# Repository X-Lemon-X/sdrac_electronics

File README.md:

# SDRAC electronic design
This repository contains the psb schematics and designs of the SDRAC board.

## SDRACboard
- Supply voltage 12-48V (9-55V)
- the board has a 5V/2A on board regualator, to power the board and peripherals
- USB-C for programming and reading data
- ST-wire pins for programming and debugging
- 3 bit hardware address CID0, CID1, CID2
- 6 pin JS connector for IO-appliacitons, with analog, UART, Timers, 5V and GND
- 2x 4 pin Molex connectors for CAN bus
- 2x 6 pin Molex connectors for I2C magnetic encoder
- 2x 2 pin Molex connectors for external temperature sensors (ntc termistors)
- 1x 4 pin Molex connector for stepper motor
- 1x 4 pin connector for external steper motor driver
- 1x Screw terminal for external steper motor driver power
- XT30-M, XT30-F  connectors for input and output power

## Schematics
The schematics are made in KiCad.

## Assembly
Manual assembly takes about 2 hours, with stemple and hot air station.

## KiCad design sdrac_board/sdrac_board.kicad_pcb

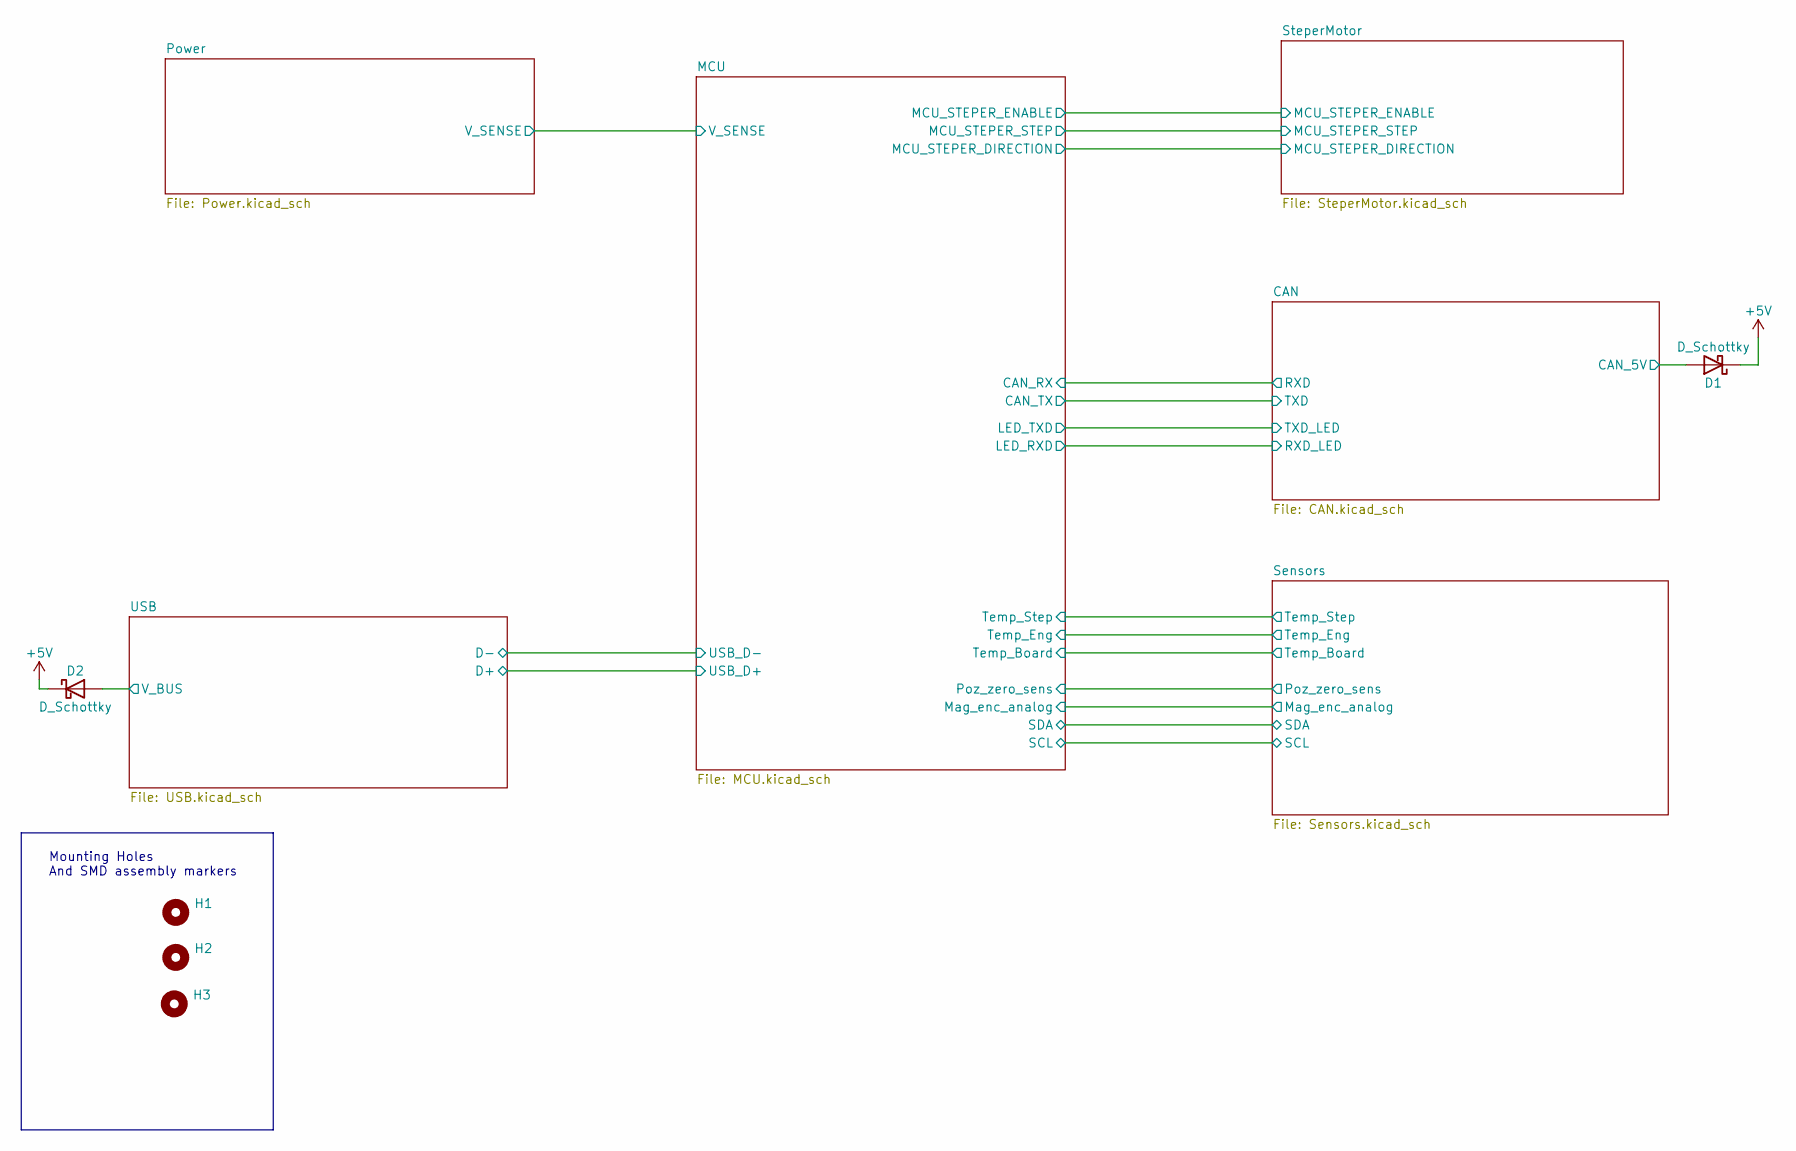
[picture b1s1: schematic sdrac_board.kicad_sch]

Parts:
D1, D2: D_Schottky; D_SMA
H1, H2, H3: MountingHole; MountingHole_3.2mm_M3_ISO7380

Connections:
+5V: D1.1 (K), D2.1 (K); also elsewhere on the board
/CAN/CAN_5V: D1.2 (A); also elsewhere on the board
/USB/V_BUS: D2.2 (A); also elsewhere on the board

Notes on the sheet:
Mounting Holes And SMD assembly markers

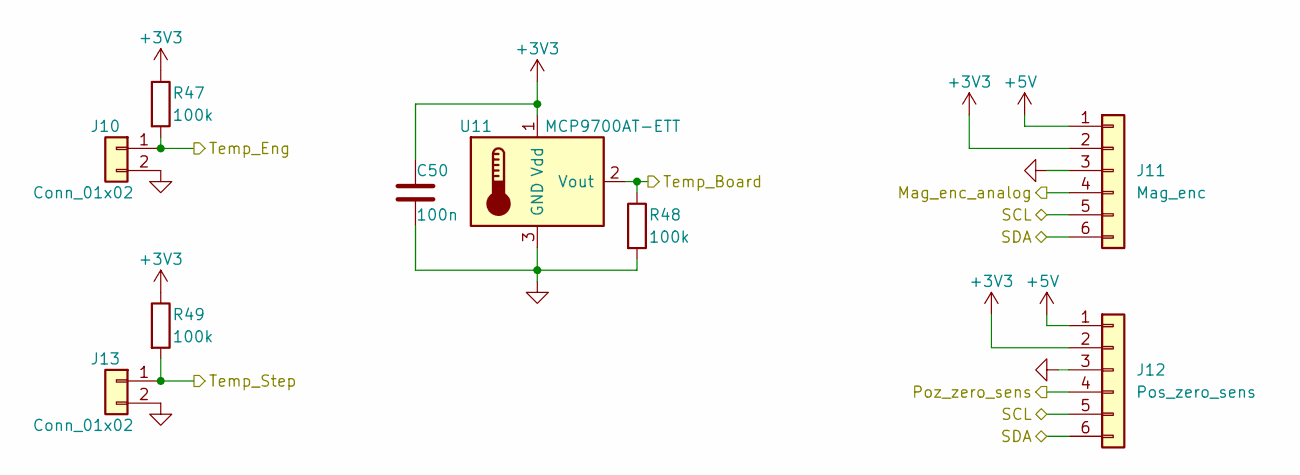
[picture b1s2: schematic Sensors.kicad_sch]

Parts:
C50: 100n; C_0402_1005Metric
J10, J13: Conn_01x02; Molex_Micro-Fit_3.0_43045-0212_2x01_P3.00mm_Vertical
J11: Mag_enc; Molex_Micro-Fit_3.0_43045-0612_2x03_P3.00mm_Vertical
J12: Pos_zero_sens; Molex_Micro-Fit_3.0_43045-0612_2x03_P3.00mm_Vertical
R47, R48, R49: 100k; R_0402_1005Metric
U11: MCP9700AT-ETT; SOT-23

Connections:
+3V3: C50.1, J11.2, J12.2, R47.1, R49.1, U11.1 (Vdd); also elsewhere on the board
+5V: J11.1, J12.1; also elsewhere on the board
/MCU/Mag_enc_analog: J11.4; also elsewhere on the board
/MCU/Poz_zero_sens: J12.4; also elsewhere on the board
/MCU/SCL: J11.5, J12.5; also elsewhere on the board
/MCU/SDA: J11.6, J12.6; also elsewhere on the board
/MCU/Temp_Board: R48.1, U11.2 (Vout); also elsewhere on the board
/MCU/Temp_Eng: J10.1, R47.2; also elsewhere on the board
/MCU/Temp_Step: J13.1, R49.2; also elsewhere on the board
GND: C50.2, J10.2, J11.3, J12.3, J13.2, R48.2, U11.3 (GND); also elsewhere on the board

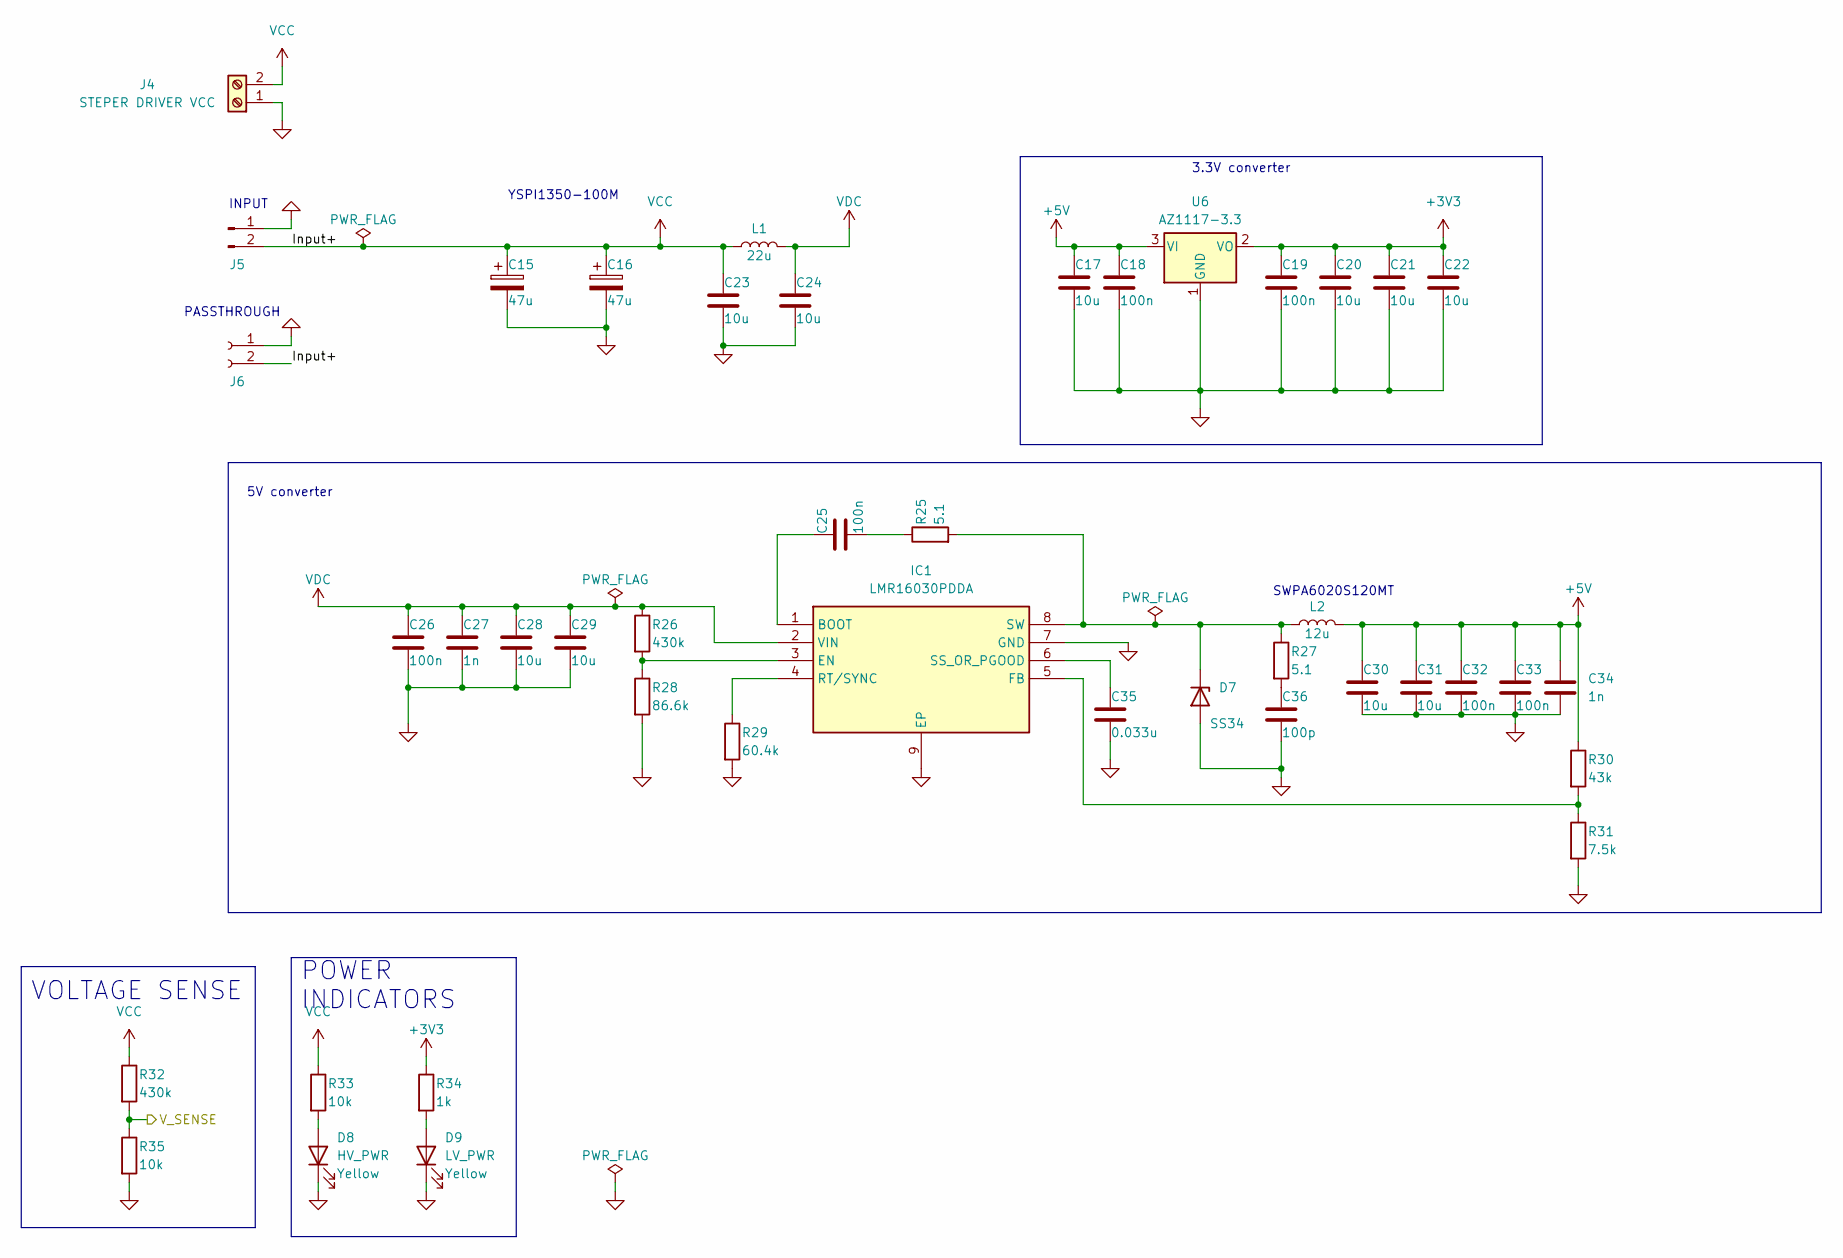
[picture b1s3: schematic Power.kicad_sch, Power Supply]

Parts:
C15, C16: 47u; CP_Elec_10x10.5
C17: 10u; C_1206_3216Metric
C18, C19, C26, C32, C33: 100n; C_0603_1608Metric
C20, C21, C22, C30, C31: 10u; C_0805_2012Metric
C23, C24, C28, C29: 10u; C_1210_3225Metric
C25: 100n; R_0603_1608Metric
C27, C34: 1n; C_0603_1608Metric
C35: 0.033u; R_0603_1608Metric
C36: 100p; C_0603_1608Metric
D7: SS34; D_SMA
D8: HV_PWR; D_0603_1608Metric
D9: LV_PWR; D_0603_1608Metric
IC1: LMR16030PDDA; SOIC127P600X170-9N; Manufacturer_Part_Number LMR16030PDDA; Mouser Part Number 595-LMR16030PDDA
J4: STEPER DRIVER VCC; TerminalBlock_Phoenix_MKDS-1,5-2_1x02_P5.00mm_Horizontal
J5: Conn_01x02_Male; AMASS_XT30PW-M_1x02_P2.50mm_Horizontal
J6: Conn_01x02_Female; AMASS_XT30PW-F_1x02_P2.50mm_Horizontal
L1: 22u; L_6.3x6.3_H3
L2: 12u; L_1812_4532Metric
R25, R27: 5.1; R_0603_1608Metric
R26, R32: 430k; R_0603_1608Metric
R28: 86.6k; R_0603_1608Metric
R29: 60.4k; R_0603_1608Metric
R30: 43k; R_0603_1608Metric
R31: 7.5k; R_0603_1608Metric
R33: 10k; R_0402_1005Metric
R34: 1k; R_0402_1005Metric
R35: 10k; R_0603_1608Metric
U6: AZ1117-3.3; SOT-223-3_TabPin2

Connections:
+3V3: C19.1, C20.1, C21.1, C22.1, R34.1, U6.2 (VO); also elsewhere on the board
+5V: C17.1, C18.1, C30.1, C31.1, C32.1, C33.1, C34.1, L2.2, R30.1, U6.3 (VI); also elsewhere on the board
/MCU/V_SENSE: R32.2, R35.1; also elsewhere on the board
GND: C15.2, C16.2, C17.2, C18.2, C19.2, C20.2, C21.2, C22.2, C23.2, C24.2, C26.2, C27.2, C28.2, C29.2, C30.2, C31.2, C32.2, C33.2, C34.2, C35.2, C36.2, D7.2 (A), D8.1 (K), D9.1 (K), IC1.7 (GND), IC1.9 (EP), J4.1, J5.1, J6.1, R28.2, R29.2, R31.2, R35.2, U6.1 (GND); also elsewhere on the board
unnamed: C25.2, R25.1
unnamed: C36.1, R27.2
unnamed: D7.1 (K), IC1.8 (SW), L2.1, R25.2, R27.1
unnamed: D8.2 (A), R33.2
unnamed: D9.2 (A), R34.2
unnamed: C25.1, IC1.1 (BOOT)
unnamed: IC1.3 (EN), R26.2, R28.1
unnamed: IC1.5 (FB), R30.2, R31.1
unnamed: IC1.4 (RT/SYNC), R29.1
unnamed: C35.1, IC1.6 (SS_OR_PGOOD)
VCC: C15.1, C16.1, C23.1, J4.2, J5.2, J6.2, L1.1, R32.1, R33.1; also elsewhere on the board
VDC: C24.1, C26.1, C27.1, C28.1, C29.1, IC1.2 (VIN), L1.2, R26.1

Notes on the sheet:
POWER INDICATORS
VOLTAGE SENSE
YSPI1350-100M
PASSTHROUGH
SWPA6020S120MT
INPUT
3.3V converter
5V converter

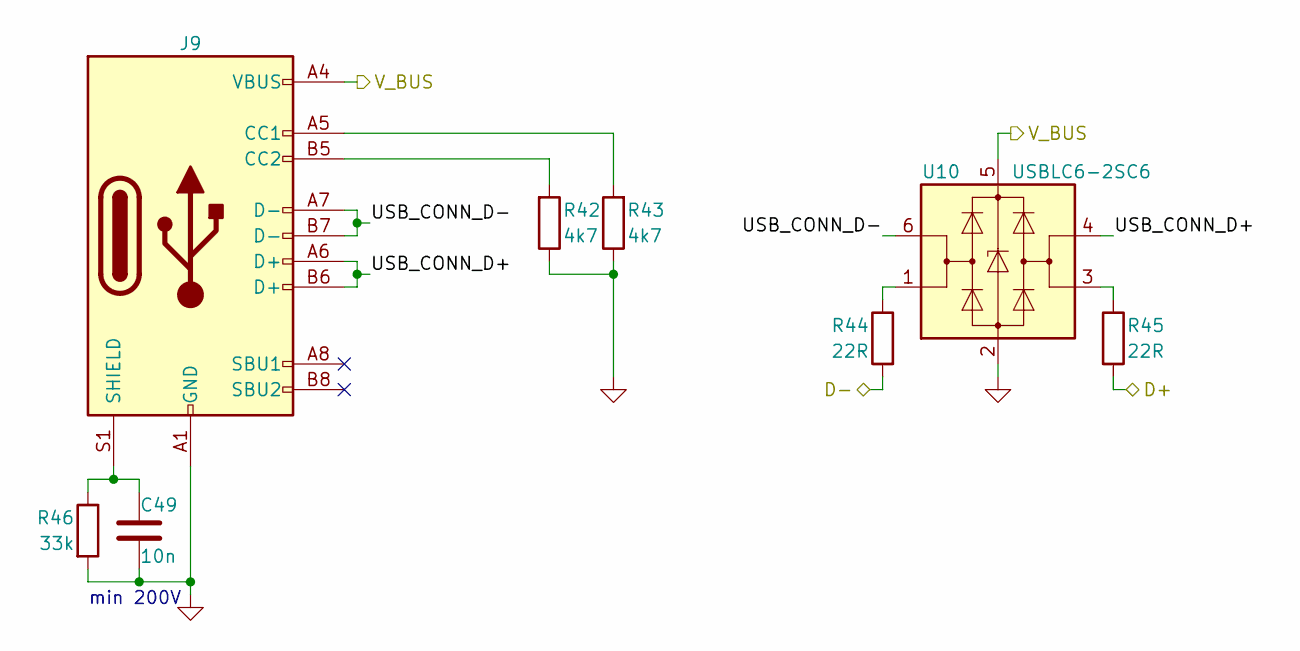
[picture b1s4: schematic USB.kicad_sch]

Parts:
C49: 10n; C_0805_2012Metric
J9: USB_C_Receptacle_USB2.0; USB_C_Receptacle_G-Switch_GT-USB-7010ASV
R42, R43: 4k7; R_0402_1005Metric
R44, R45: 22R; R_0402_1005Metric
R46: 33k; R_0603_1608Metric
U10: USBLC6-2SC6; SOT-23-6

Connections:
/MCU/USB_D+: R45.2; also elsewhere on the board
/MCU/USB_D-: R44.2; also elsewhere on the board
/USB/USB_CONN_D+: J9.A6 (D+), J9.B6 (D+), U10.4 (I/O2)
/USB/USB_CONN_D-: J9.A7 (D-), J9.B7 (D-), U10.6 (I/O1)
/USB/V_BUS: J9.A4 (VBUS), J9.A9 (VBUS), J9.B4 (VBUS), J9.B9 (VBUS), U10.5 (VBUS); also elsewhere on the board
GND: C49.2, J9.A1 (GND), J9.A12 (GND), J9.B1 (GND), J9.B12 (GND), R42.1, R43.1, R46.2, U10.2 (GND); also elsewhere on the board
unnamed: J9.A5 (CC1), R43.2
unnamed: J9.B5 (CC2), R42.2
unnamed: C49.1, J9.S1 (SHIELD), R46.1
unnamed: R44.1, U10.1 (I/O1)
unnamed: R45.1, U10.3 (I/O2)

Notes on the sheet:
min 200V

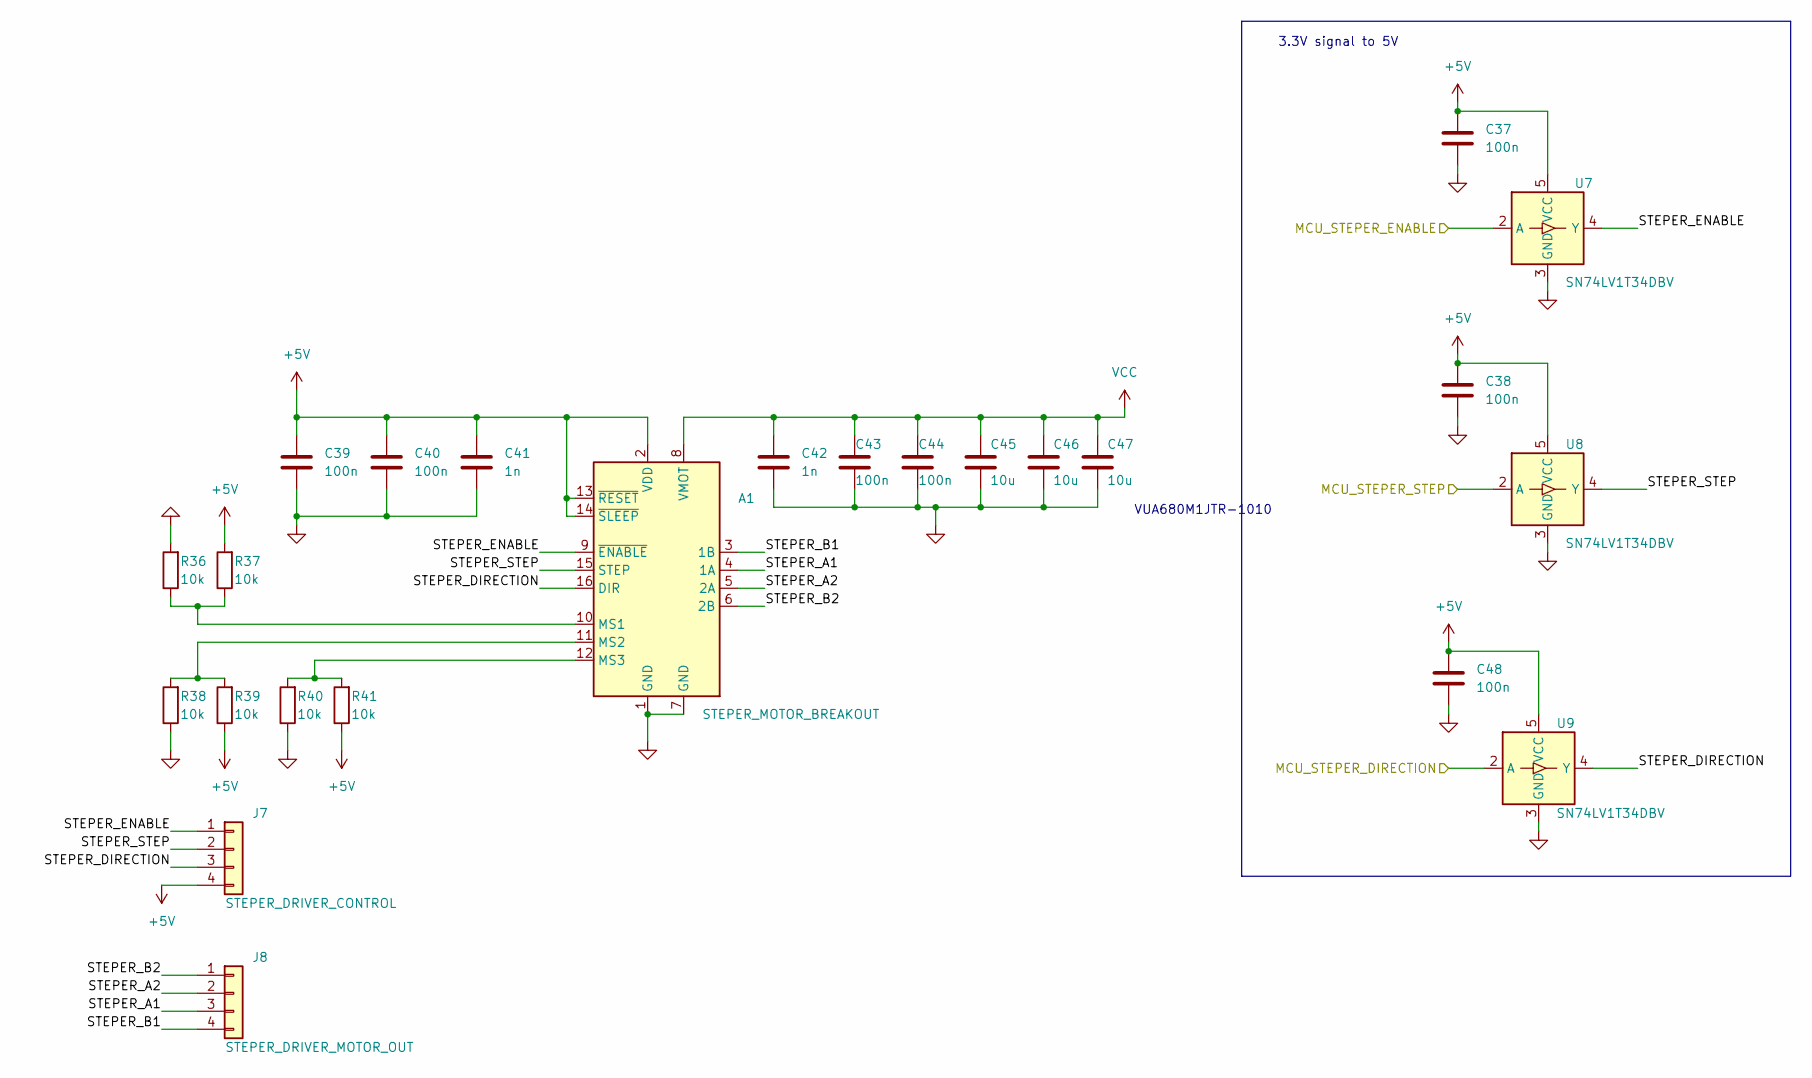
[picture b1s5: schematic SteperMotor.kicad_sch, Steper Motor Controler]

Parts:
A1: STEPER_MOTOR_BREAKOUT; Pololu_Breakout-16_15.2x20.3mm
C37, C38, C48: 100n; C_0402_1005Metric
C39, C40: 100n; C_0402_1005Metric_Pad0.74x0.62mm_HandSolder
C41: 1n; C_0402_1005Metric
C42: 1n; C_1206_3216Metric
C43, C44: 100n; C_1206_3216Metric
C45, C46, C47: 10u; C_1210_3225Metric
J7: STEPER_DRIVER_CONTROL; Molex_Micro-Fit_3.0_43045-0412_2x02_P3.00mm_Vertical
J8: STEPER_DRIVER_MOTOR_OUT; Molex_Micro-Fit_3.0_43045-0412_2x02_P3.00mm_Vertical
R36, R37, R38, R39, R40, R41: 10k; R_0402_1005Metric
U7, U8, U9: SN74LV1T34DBV; SOT-23-5

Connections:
+5V: A1.2 (VDD), A1.13 (~RESET), A1.14 (~SLEEP), C37.1, C38.1, C39.1, C40.1, C41.1, C48.1, J7.4, R37.2, R39.1, R41.1, U7.5 (VCC), U8.5 (VCC), U9.5 (VCC); also elsewhere on the board
/MCU/MCU_STEPER_DIRECTION: U9.2 (A); also elsewhere on the board
/MCU/MCU_STEPER_ENABLE: U7.2 (A); also elsewhere on the board
/MCU/MCU_STEPER_STEP: U8.2 (A); also elsewhere on the board
/SteperMotor/STEPER_A1: A1.4 (1A), J8.3
/SteperMotor/STEPER_A2: A1.5 (2A), J8.2
/SteperMotor/STEPER_B1: A1.3 (1B), J8.4
/SteperMotor/STEPER_B2: A1.6 (2B), J8.1
/SteperMotor/STEPER_DIRECTION: A1.16 (DIR), J7.3, U9.4 (Y)
/SteperMotor/STEPER_ENABLE: A1.9 (~ENABLE), J7.1, U7.4 (Y)
/SteperMotor/STEPER_STEP: A1.15 (STEP), J7.2, U8.4 (Y)
GND: A1.1 (GND), A1.7 (GND), C37.2, C38.2, C39.2, C40.2, C41.2, C42.2, C43.2, C44.2, C45.2, C46.2, C47.2, C48.2, R36.2, R38.1, R40.1, U7.3 (GND), U8.3 (GND), U9.3 (GND); also elsewhere on the board
unnamed: A1.10 (MS1), R36.1, R37.1
unnamed: A1.11 (MS2), R38.2, R39.2
unnamed: A1.12 (MS3), R40.2, R41.2
VCC: A1.8 (VMOT), C42.1, C43.1, C44.1, C45.1, C46.1, C47.1; also elsewhere on the board

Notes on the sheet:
3.3V signal to 5V
VUA680M1JTR-1010

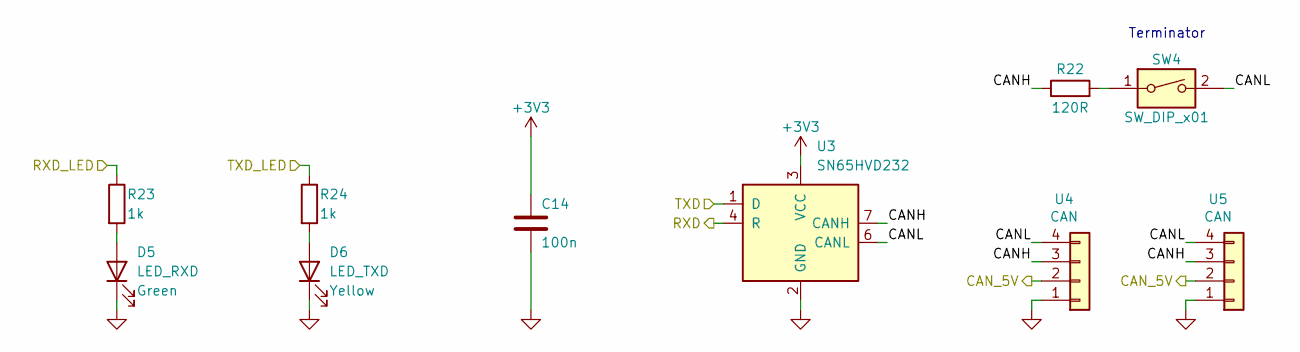
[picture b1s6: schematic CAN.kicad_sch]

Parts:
C14: 100n; C_0402_1005Metric
D5: LED_RXD; D_0603_1608Metric
D6: LED_TXD; D_0603_1608Metric
R22: 120R; R_0603_1608Metric
R23, R24: 1k; R_0402_1005Metric
SW4: SW_DIP_x01; SW_DIP_SPSTx01_Slide_6.7x4.1mm_W6.73mm_P2.54mm_LowProfile_J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
U3: SN65HVD232; SOIC-8_3.9x4.9mm_P1.27mm
U4, U5: CAN; Molex_Micro-Fit_3.0_43045-0412_2x02_P3.00mm_Vertical

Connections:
+3V3: C14.1, U3.3 (VCC); also elsewhere on the board
/CAN/CANH: R22.1, U3.7 (CANH), U4.3, U5.3
/CAN/CANL: SW4.2, U3.6 (CANL), U4.4, U5.4
/CAN/CAN_5V: U4.2, U5.2; also elsewhere on the board
/CAN/RXD: U3.4 (R); also elsewhere on the board
/CAN/RXD_LED: R23.1; also elsewhere on the board
/CAN/TXD: U3.1 (D); also elsewhere on the board
/CAN/TXD_LED: R24.1; also elsewhere on the board
GND: C14.2, D5.1 (K), D6.1 (K), U3.2 (GND), U4.1, U5.1; also elsewhere on the board
unnamed: D5.2 (A), R23.2
unnamed: D6.2 (A), R24.2
unnamed: R22.2, SW4.1

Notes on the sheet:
Terminator

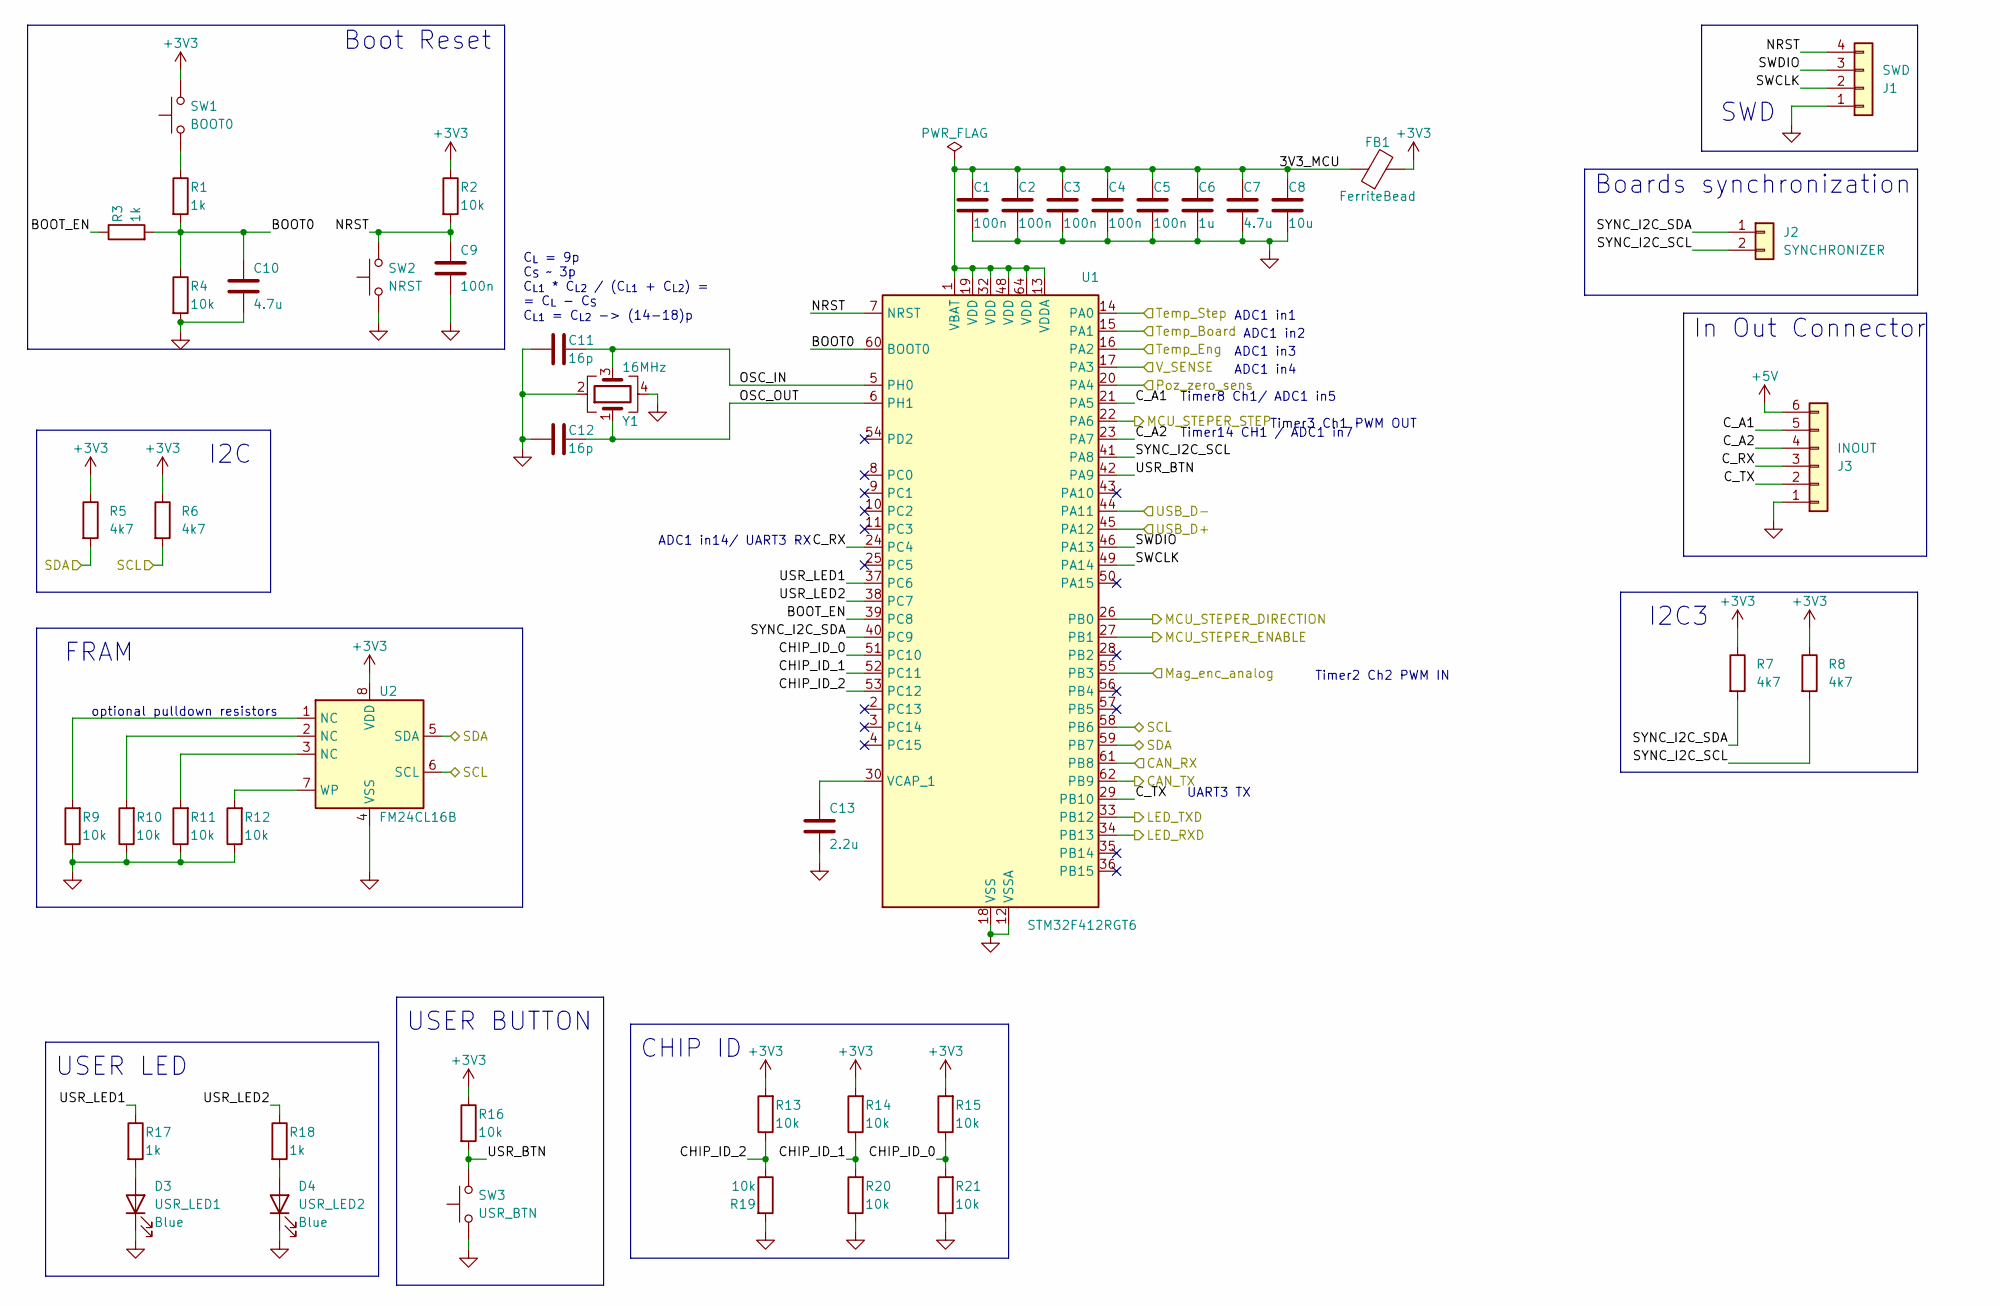
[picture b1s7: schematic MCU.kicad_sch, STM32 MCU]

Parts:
C1, C2, C3, C4, C5, C9: 100n; C_0402_1005Metric
C6: 1u; C_0603_1608Metric
C7: 4.7u; C_0603_1608Metric
C8: 10u; C_0805_2012Metric
C10: 4.7u; C_0402_1005Metric
C11, C12: 16p; C_0402_1005Metric
C13: 2.2u; C_0603_1608Metric
D3: USR_LED1; D_0603_1608Metric
D4: USR_LED2; D_0603_1608Metric
FB1: FerriteBead; L_0805_2012Metric
J1: SWD; PinHeader_1x04_P2.54mm_Vertical
J2: SYNCHRONIZER; JST_XH_B2B-XH-A_1x02_P2.50mm_Vertical
J3: INOUT; JST_XH_B6B-XH-A_1x06_P2.50mm_Vertical
R1, R3, R17, R18: 1k; R_0402_1005Metric
R2, R4, R9, R10, R11, R12, R13, R14, R15, R16, R19, R20, R21: 10k; R_0402_1005Metric
R5, R6, R7, R8: 4k7; R_0402_1005Metric
SW1: BOOT0; SW_SPST_PTS810
SW2: NRST; SW_SPST_PTS810
SW3: USR_BTN; SW_SPST_PTS810
U1: STM32F412RGT6; LQFP-64_10x10mm_P0.5mm
U2: FM24CL16B; SOIC-8_3.9x4.9mm_P1.27mm
Y1: 16MHz; Crystal_SMD_3225-4Pin_3.2x2.5mm

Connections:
+3V3: FB1.2, R2.1, R5.1, R6.1, R7.1, R8.1, R13.2, R14.2, R15.2, R16.1, SW1.2, U2.8 (VDD); also elsewhere on the board
+5V: J3.6; also elsewhere on the board
/CAN/RXD: U1.61 (PB8); also elsewhere on the board
/CAN/RXD_LED: U1.34 (PB13); also elsewhere on the board
/CAN/TXD: U1.62 (PB9); also elsewhere on the board
/CAN/TXD_LED: U1.33 (PB12); also elsewhere on the board
/MCU/3V3_MCU: C1.1, C2.1, C3.1, C4.1, C5.1, C6.1, C7.1, C8.1, FB1.1, U1.1 (VBAT), U1.13 (VDDA), U1.19 (VDD), U1.32 (VDD), U1.48 (VDD), U1.64 (VDD)
/MCU/BOOT0: C10.1, R1.2, R3.2, R4.1, U1.60 (BOOT0)
/MCU/BOOT_EN: R3.1, U1.39 (PC8)
/MCU/CHIP_ID_0: R15.1, R21.2, U1.51 (PC10)
/MCU/CHIP_ID_1: R14.1, R20.2, U1.52 (PC11)
/MCU/CHIP_ID_2: R13.1, R19.1, U1.53 (PC12)
/MCU/C_A1: J3.5, U1.21 (PA5)
/MCU/C_A2: J3.4, U1.23 (PA7)
/MCU/C_RX: J3.3, U1.24 (PC4)
/MCU/C_TX: J3.2, U1.29 (PB10)
/MCU/MCU_STEPER_DIRECTION: U1.26 (PB0); also elsewhere on the board
/MCU/MCU_STEPER_ENABLE: U1.27 (PB1); also elsewhere on the board
/MCU/MCU_STEPER_STEP: U1.22 (PA6); also elsewhere on the board
/MCU/Mag_enc_analog: U1.55 (PB3); also elsewhere on the board
/MCU/NRST: C9.1, J1.4, R2.2, SW2.2, U1.7 (NRST)
/MCU/OSC_IN: C11.2, U1.5 (PH0), Y1.3
/MCU/OSC_OUT: C12.2, U1.6 (PH1), Y1.1
/MCU/Poz_zero_sens: U1.20 (PA4); also elsewhere on the board
/MCU/SCL: R6.2, U1.58 (PB6), U2.6 (SCL); also elsewhere on the board
/MCU/SDA: R5.2, U1.59 (PB7), U2.5 (SDA); also elsewhere on the board
/MCU/SWCLK: J1.2, U1.49 (PA14)
/MCU/SWDIO: J1.3, U1.46 (PA13)
/MCU/SYNC_I2C_SCL: J2.2, R8.2, U1.41 (PA8)
/MCU/SYNC_I2C_SDA: J2.1, R7.2, U1.40 (PC9)
/MCU/Temp_Board: U1.15 (PA1); also elsewhere on the board
/MCU/Temp_Eng: U1.16 (PA2); also elsewhere on the board
/MCU/Temp_Step: U1.14 (PA0); also elsewhere on the board
/MCU/USB_D+: U1.45 (PA12); also elsewhere on the board
/MCU/USB_D-: U1.44 (PA11); also elsewhere on the board
/MCU/USR_BTN: R16.2, SW3.2, U1.42 (PA9)
/MCU/USR_LED1: R17.1, U1.37 (PC6)
/MCU/USR_LED2: R18.1, U1.38 (PC7)
/MCU/V_SENSE: U1.17 (PA3); also elsewhere on the board
GND: C1.2, C2.2, C3.2, C4.2, C5.2, C6.2, C7.2, C8.2, C9.2, C10.2, C11.1, C12.1, C13.2, D3.1 (K), D4.1 (K), J1.1, J3.1, R4.2, R9.1, R10.1, R11.1, R12.1, R19.2, R20.1, R21.1, SW2.1, SW3.1, U1.12 (VSSA), U1.18 (VSS), U1.31 (VSS), U1.47 (VSS), U1.63 (VSS), U2.4 (VSS), Y1.2, Y1.4; also elsewhere on the board
unnamed: D3.2 (A), R17.2
unnamed: D4.2 (A), R18.2
unnamed: R1.1, SW1.1
unnamed: R9.2, U2.1 (NC)
unnamed: R10.2, U2.2 (NC)
unnamed: R11.2, U2.3 (NC)
unnamed: C13.1, U1.30 (VCAP_1)
unnamed: R12.2, U2.7 (WP)

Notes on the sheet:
UART3 TX
FRAM
Timer2 Ch2 PWM IN
Timer3 Ch1 PWM OUT
C_{L} = 9p C_{S} ~ 3p C_{L1} * C_{L2} / (C_{L1} + C_{L2}) = = C_{L} - C_{S} C_{L1} = C_{L2} -> (14-18)p
In Out Connector
optional pulldown resistors
I2C3
Boot Reset
ADC1 in3
CHIP ID
Timer14 CH1 / ADC1 in7
SWD
USER LED
USER BUTTON
ADC1 in4
ADC1 in14/ UART3 RX
Timer8 Ch1/ ADC1 in5
ADC1 in1
ADC1 in2
I2C
Boards synchronization

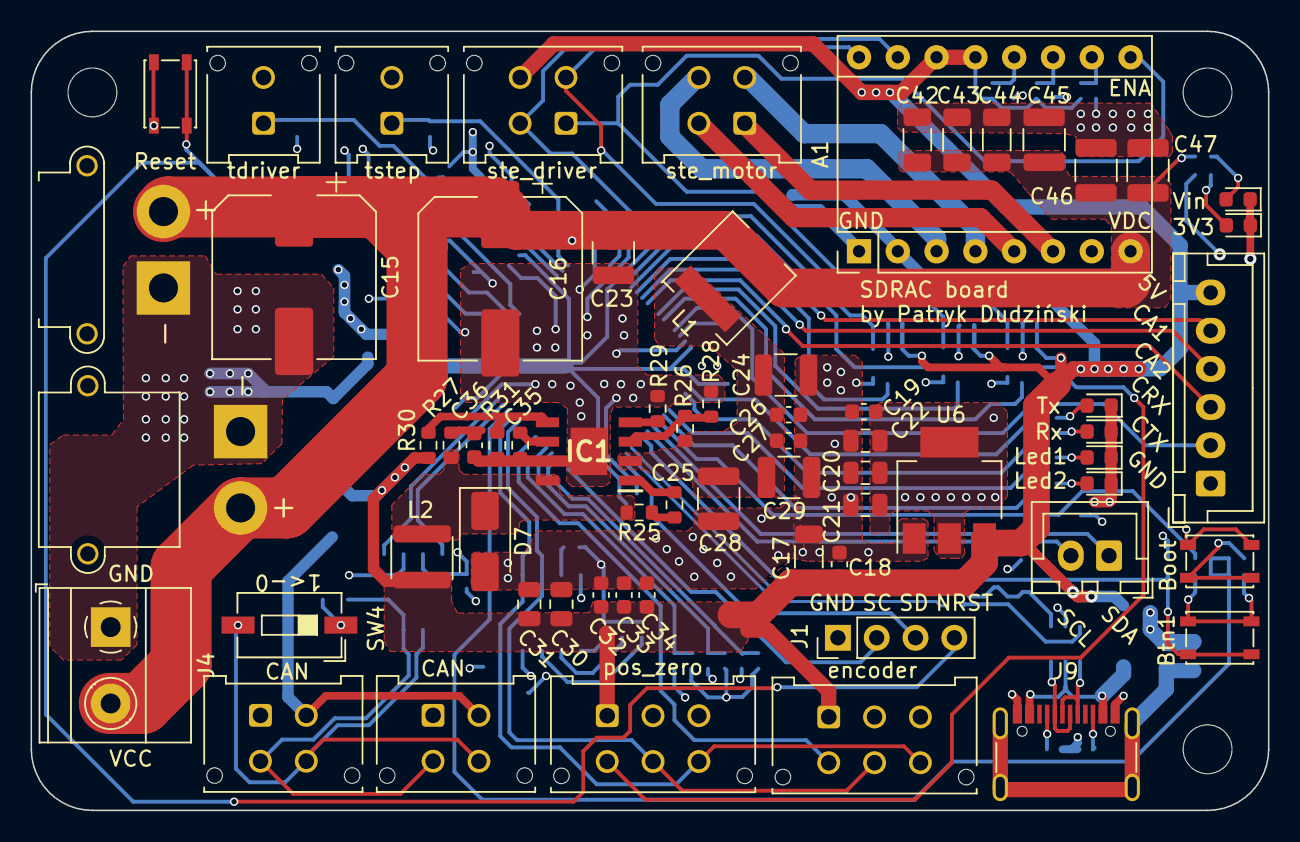
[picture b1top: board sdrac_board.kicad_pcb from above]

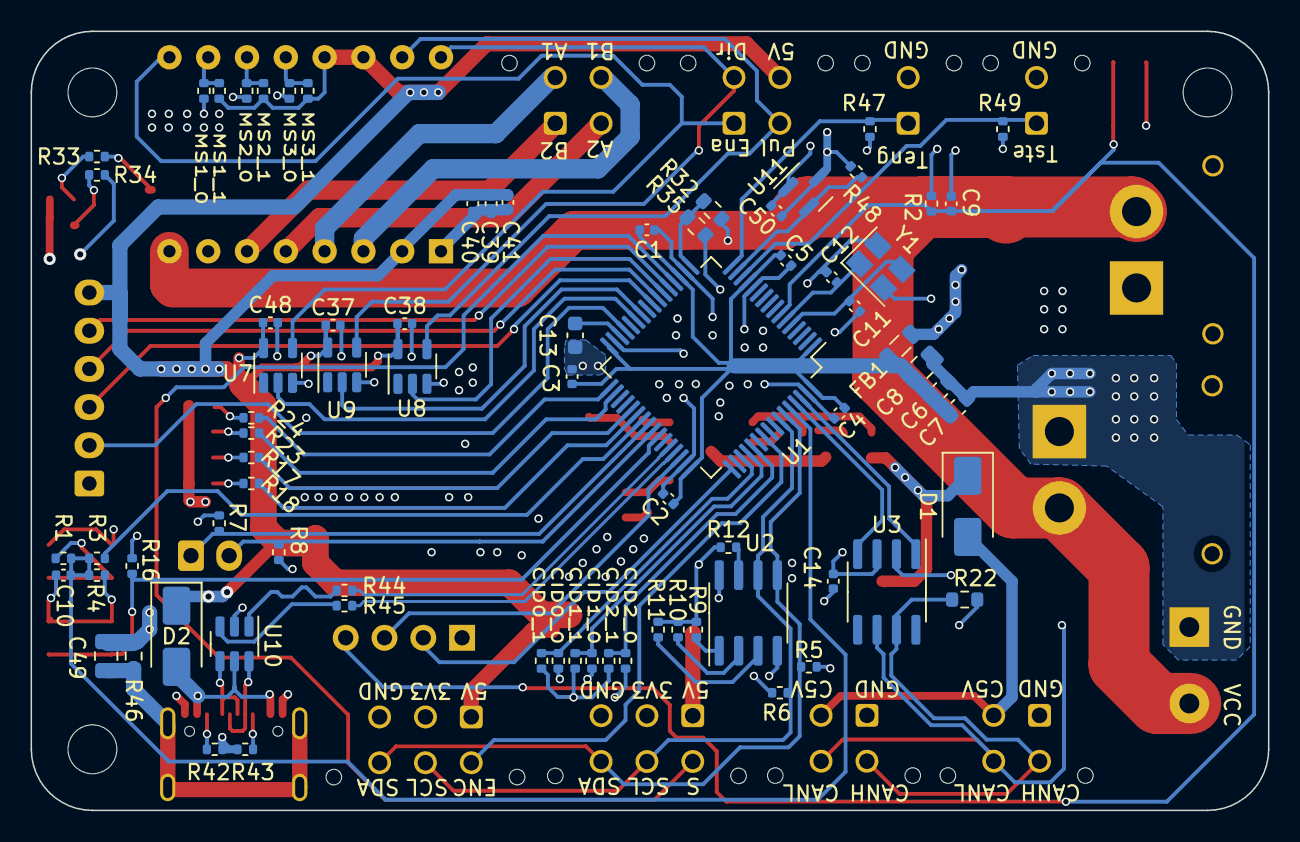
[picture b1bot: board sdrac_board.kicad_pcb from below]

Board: 4 copper layers, 81.0 x 51.0 mm, 145 parts (76 on the bottom side), 84 nets.

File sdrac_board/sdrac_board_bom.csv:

"Id";"Designator";"Footprint";"Quantity";"Designation";"Supplier and ref";
1;"R28";"R_0603_1608Metric";1;"86.6k";;;
2;"U4,U5";"Molex_Micro-Fit_3.0_43045-0412_2x02_P3.00mm_Vertical";2;"CAN";;;
3;"R29";"R_0603_1608Metric";1;"60.4k";;;
4;"U6";"SOT-223-3_TabPin2";1;"AZ1117-3.3";;;
5;"J6";"AMASS_XT30PW-F_1x02_P2.50mm_Horizontal";1;"Conn_01x02_Female";;;
6;"J8";"Molex_Micro-Fit_3.0_43045-0412_2x02_P3.00mm_Vertical";1;"STEPER_DRIVER_MOTOR_OUT";;;
7;"SW4";"SW_DIP_SPSTx01_Slide_6.7x4.1mm_W6.73mm_P2.54mm_LowProfile_JPin";1;"SW_DIP_x01";;;
8;"D6";"D_0603_1608Metric";1;"LED_TXD";;;
9;"C16,C15";"CP_Elec_10x10.5";2;"47u";;;
10;"J5";"AMASS_XT30PW-M_1x02_P2.50mm_Horizontal";1;"Conn_01x02_Male";;;
11;"R30,R32";"R_0603_1608Metric";2;"43k";;;
12;"C35";"R_0603_1608Metric";1;"0.033u";;;
13;"C33,C18,C26,C32,C19";"C_0603_1608Metric";5;"100n";;;
14;"C43,C44";"C_1206_3216Metric";2;"100n";;;
15;"C47,C23,C29,C28,C46,C24,C45";"C_1210_3225Metric";7;"10u";;;
16;"J12";"Molex_Micro-Fit_3.0_43045-0612_2x03_P3.00mm_Vertical";1;"Pos_zero_sens";;;
17;"D3";"D_0603_1608Metric";1;"USR_LED1";;;
18;"C25";"R_0603_1608Metric";1;"100n";;;
19;"C17";"C_1206_3216Metric";1;"10u";;;
20;"C34,C27";"C_0603_1608Metric";2;"1n";;;
21;"SW2";"SW_SPST_PTS810";1;"NRST";;;
22;"SW1";"SW_SPST_PTS810";1;"BOOT0";;;
23;"C30,C21,C31,C22,C20,C8";"C_0805_2012Metric";6;"10u";;;
24;"R26";"R_0603_1608Metric";1;"430k";;;
25;"R31";"R_0603_1608Metric";1;"7.5k";;;
26;"D7";"D_SMA";1;"SS34";;;
27;"SW3";"SW_SPST_PTS810";1;"USR_BTN";;;
28;"H1,H2,H3";"MountingHole_3.2mm_M3_ISO7380";3;"MountingHole";;;
29;"R27,R25";"R_0603_1608Metric";2;"5.1";;;
30;"J11";"Molex_Micro-Fit_3.0_43045-0612_2x03_P3.00mm_Vertical";1;"Mag_enc";;;
31;"IC1";"SOIC127P600X170-9N";1;"LMR16030PDDA";;;
32;"J1";"PinHeader_1x04_P2.54mm_Vertical";1;"SWD";;;
33;"J9";"USB_C_Receptacle_G-Switch_GT-USB-7010ASV";1;"USB_C_Receptacle_USB2.0";;;
34;"J7";"Molex_Micro-Fit_3.0_43045-0412_2x02_P3.00mm_Vertical";1;"STEPER_DRIVER_CONTROL";;;
35;"L1";"L_6.3x6.3_H3";1;"22u";;;
36;"J3";"JST_XH_B6B-XH-A_1x06_P2.50mm_Vertical";1;"INOUT";;;
37;"D9";"D_0603_1608Metric";1;"LV_PWR";;;
38;"D8";"D_0603_1608Metric";1;"HV_PWR";;;
39;"D4";"D_0603_1608Metric";1;"USR_LED2";;;
40;"L2";"L_1812_4532Metric";1;"12u";;;
41;"J4";"TerminalBlock_Phoenix_MKDS-1,5-2_1x02_P5.00mm_Horizontal";1;"STEPER DRIVER VCC";;;
42;"A1";"Pololu_Breakout-16_15.2x20.3mm";1;"STEPER_MOTOR_BREAKOUT";;;
43;"J10,J13";"Molex_Micro-Fit_3.0_43045-0212_2x01_P3.00mm_Vertical";2;"Conn_01x02";;;
44;"C36";"C_0603_1608Metric";1;"100p";;;
45;"D5";"D_0603_1608Metric";1;"LED_RXD";;;
46;"C42";"C_1206_3216Metric";1;"1n";;;
47;"J2";"JST_XH_B2B-XH-A_1x02_P2.50mm_Vertical";1;"SYNCHRONIZER";;;
48;"U3";"SOIC-8_3.9x4.9mm_P1.27mm";1;"SN65HVD232";;;
49;"R48,R47,R49";"R_0402_1005Metric";3;"100k";;;
50;"R6,R8,R7,R5";"R_0402_1005Metric";4;"4k7";;;
51;"C39,C40";"C_0402_1005Metric_Pad0.74x0.62mm_HandSolder";2;"100n";;;
52;"U7,U9,U8";"SOT-23-5";3;"SN74LV1T34DBV";;;
53;"U11";"SOT-23";1;"MCP9700AT-ETT";;;
54;"R3,R23,R34,R1,R17,R24,R18";"R_0402_1005Metric";7;"1k";;;
55;"R2,R4,R16,R19,R36,R13,R41,R20,R10,R15,R40,R39,R11,R12,R14,R33,R37,R9,R21,R38";"R_0402_1005Metric";20;"10k";;;
56;"R45,R44";"R_0402_1005Metric";2;"22R";;;
57;"R22";"R_0603_1608Metric";1;"120R";;;
58;"U1";"LQFP-64_10x10mm_P0.5mm";1;"STM32F412RGT6";;;
59;"R43,R42";"R_0402_1005Metric";2;"5k1";;;
60;"C2,C37,C9,C1,C50,C4,C14,C48,C5,C3,C38";"C_0402_1005Metric";11;"100n";;;
61;"D2,D1";"D_SMA";2;"D_Schottky";;;
62;"R46";"R_0603_1608Metric";1;"33k";;;
63;"C11,C12";"C_0402_1005Metric";2;"16p";;;
64;"C6";"C_0603_1608Metric";1;"1u";;;
65;"C49";"C_0805_2012Metric";1;"10n";;;
66;"R35";"R_0603_1608Metric";1;"1k";;;
67;"C41";"C_0402_1005Metric";1;"1n";;;
68;"C7";"C_0603_1608Metric";1;"4.7u";;;
69;"U10";"SOT-23-6";1;"USBLC6-2SC6";;;
70;"C10";"C_0402_1005Metric";1;"4.7u";;;
71;"C13";"C_0603_1608Metric";1;"2.2u";;;
72;"Y1";"Crystal_SMD_3225-4Pin_3.2x2.5mm";1;"16MHz";;;
73;"U2";"SOIC-8_3.9x4.9mm_P1.27mm";1;"FM24CL16B";;;
74;"FB1";"L_0805_2012Metric";1;"FerriteBead";;;

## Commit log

2024-03-08 init commit added all fiels
2024-03-12 fixed caps and added nreset
2024-03-15 added stuff
2024-03-15 added git ignore
2024-03-18 addded 6pin conenctor
2024-03-18 updated stuf
2024-03-20 stuff
2024-03-20 made critical changes
2024-04-15 nothing done
2024-04-17 added second I2C communscation lane for synchronization and added wyas to change mcirosteping with resistors
2024-04-20 added hardware address selector
2024-04-20 save
2024-04-22 rozlałem i wylałem wszystko xd
2024-04-27 added 10A screw terminal
2024-06-11 added datasheets
2024-06-11 fixwed resistors values
2024-06-11 added raadme
2024-06-11 update raadme
